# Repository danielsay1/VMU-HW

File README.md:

# Vehicle Measurement Unit - Hardware

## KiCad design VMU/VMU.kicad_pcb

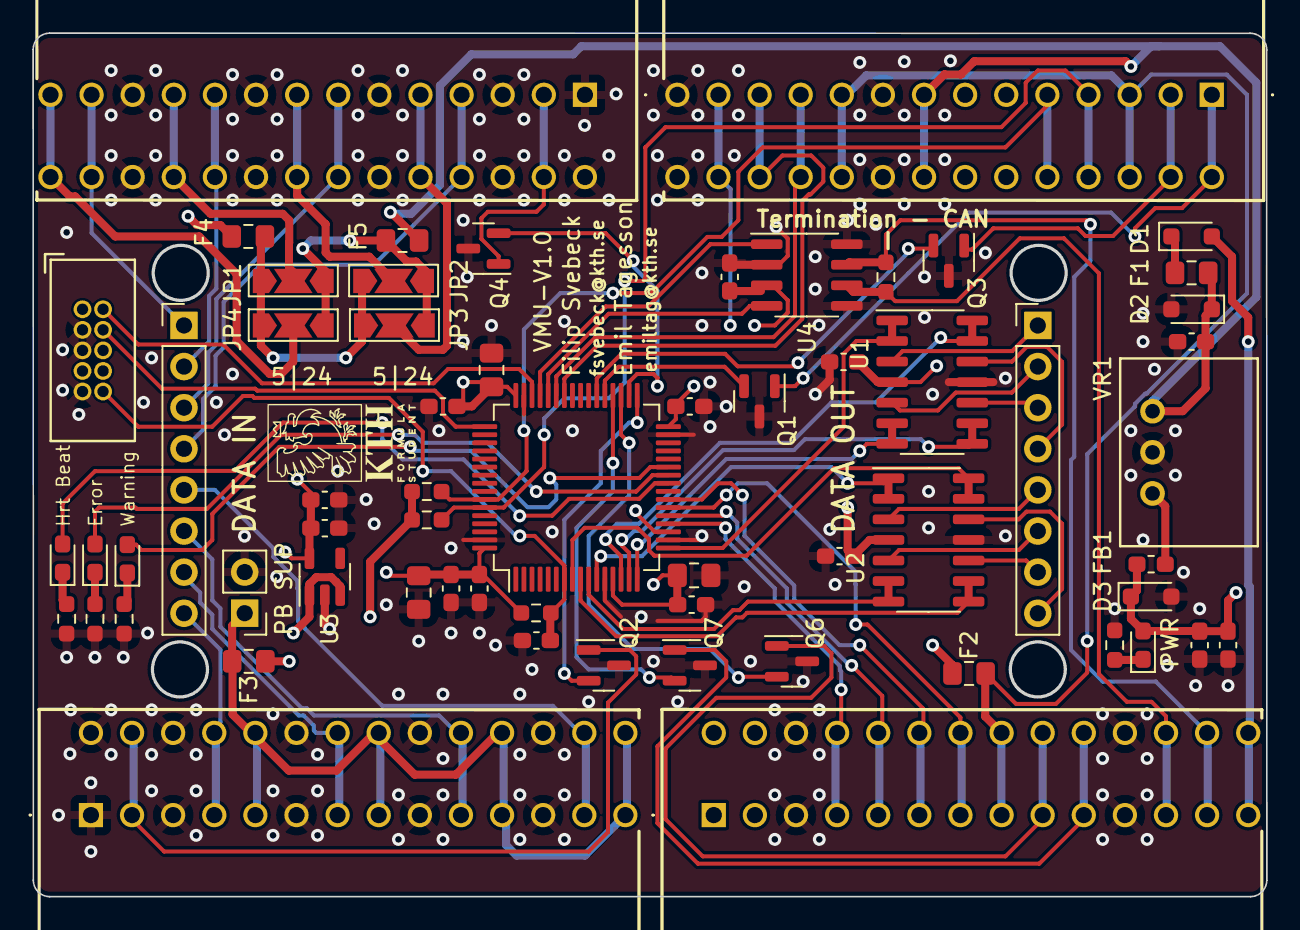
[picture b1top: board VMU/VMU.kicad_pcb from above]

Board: 4 copper layers, 76.1 x 53.2 mm, 62 parts (0 on the bottom side), 73 nets.

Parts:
C1, C2, C5, C7, C8, C9, C10, C11, C12, C13: 100n; C_0603_1608Metric_Pad1.08x0.95mm_HandSolder
C3, C4, C6: 1u; C_0603_1608Metric_Pad1.08x0.95mm_HandSolder
C14: 10n; C_0603_1608Metric_Pad1.08x0.95mm_HandSolder
C15, C16: 4.7u; C_0805_2012Metric_Pad1.18x1.45mm_HandSolder
C17: 1u; C_0805_2012Metric_Pad1.18x1.45mm_HandSolder
D1: D_Schottky; D_SOD-323_HandSoldering
D2, D3: D_TVS; D_SOD-323_HandSoldering
F1, F2, F3, F4, F5: Fuse; Fuse_0805_2012Metric_Pad1.15x1.40mm_HandSolder
FB1: FerriteBead; L_0603_1608Metric_Pad1.05x0.95mm_HandSolder
J1, J2, J6, J7: TBL009-254-14GY-2GY; TBL00925414GY2GY
J3, J4: Conn_01x08_Pin; PinHeader_1x08_P2.54mm_Vertical
J5: Conn_01x02_Pin; PinHeader_1x02_P2.54mm_Vertical
J8: ARM_JTAG_SWD_10; Atmel_ICP_connector
JP1, JP2, JP3, JP4: Jumper_3_Open; SolderJumper-3_P2.0mm_Open_TrianglePad1.0x1.5mm_NumberLabels
Q1, Q2, Q3, Q4, Q6, Q7: NMOS; SOT-23
R1: 510; R_0603_1608Metric_Pad0.98x0.95mm_HandSolder
R2: 120; R_0603_1608Metric_Pad0.98x0.95mm_HandSolder
R3: 10k; R_0603_1608Metric_Pad0.98x0.95mm_HandSolder
R4, R5, R6: 1k; R_0603_1608Metric_Pad0.98x0.95mm_HandSolder
R7, R8: 2k7; R_0603_1608Metric_Pad0.98x0.95mm_HandSolder
U1, U2: TLV9064; SOIC-14_3.9x8.7mm_P1.27mm
U3: ADP150AUJZ-3.3-R7; SOT-23-5
U4: SN65HVD233; SOIC-8_3.9x4.9mm_P1.27mm
U5: STM32F091RCTx; LQFP-64_10x10mm_P0.5mm
VR1: Wurth-FDSM
locked: BLUE; D_0603_1608Metric_Pad1.05x0.95mm_HandSolder
locked#2: YELLOW; D_0603_1608Metric_Pad1.05x0.95mm_HandSolder
locked#3, locked#4: RED; D_0603_1608Metric_Pad1.05x0.95mm_HandSolder

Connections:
+3.3V: C6.1, C7.1, C8.2, C10.1, C11.1, C12.1, C13.1, C14.1, C15.1, C16.1, C17.1, J2.25, J2.26, J8.1 (VTref), R3.1, U3.5 (VOUT), U4.3 (VCC), U5.13 (VDDA), U5.19 (VDD), U5.32 (VDD), U5.48 (VDDIO2), U5.64 (VDD)
+5V: C1.1, C2.1, C4.1, C5.1, D3.1 (A1), F2.1, F3.1, F4.1, FB1.2, J2.11, J2.12, J2.13, J2.14, J6.1, J6.2, J6.3, J6.4, R7.1, R8.1, U1.4 (V+), U2.4 (V+), U3.1 (VIN), U3.3 (EN), locked#4.2 (A)
+24V: C3.1, D2.1 (A1), F1.1, F5.1, J2.15, J2.16, VR1.1 (IN)
/ANALOG_1_SIGNAL: J1.25, J1.26, J3.1
/ANALOG_2_SIGNAL: J1.19, J1.20, J3.2
/ANALOG_3_SIGNAL: J1.13, J1.14, J3.3
/ANALOG_4_SIGNAL: J1.7, J1.8, J3.4
/ANALOG_5_SIGNAL: J3.5, J7.25, J7.26
/ANALOG_6_SIGNAL: J3.6, J7.19, J7.20
/ANALOG_7_SIGNAL: J3.7, J7.13, J7.14
/ANALOG_8_SIGNAL: J3.8, J7.7, J7.8
/CAN1_H: J6.25, J6.26, R2.1, U4.7 (CANH)
/CAN1_L: J6.23, J6.24, R2.2, U4.6 (CANL)
/DIGITAL_SUPPLY_1: F2.2, J2.5, J2.6, J2.19, J2.20, J6.15, J6.16
/GPIO_GND_1: J7.3, J7.4, Q2.1 (D)
/GPIO_GND_2: J1.3, J1.4, Q4.1 (D)
/GPIO_GND_3: J6.17, J6.18, Q6.1 (D)
/GPIO_GND_4: J6.19, J6.20, Q7.1 (D)
/GPIO_GND_5: J2.1, J2.2, Q1.1 (D)
/GPIO_GND_6: J2.3, J2.4, Q3.1 (D)
/I2C_SCL: J2.9, J2.10, R8.2, U5.58 (PB6)
/I2C_SDA: J2.7, J2.8, R7.2, U5.59 (PB7)
/MCU/ANALOG_1: U1.1, U1.2 (-), U5.17 (PA3)
/MCU/ANALOG_2: U1.6 (-), U1.7, U5.16 (PA2)
/MCU/ANALOG_3: U1.8, U1.9 (-), U5.15 (PA1)
/MCU/ANALOG_4: U1.13 (-), U1.14, U5.14 (PA0)
/MCU/ANALOG_5: U2.1, U2.2 (-), U5.11 (PC3)
/MCU/ANALOG_6: U2.6 (-), U2.7, U5.10 (PC2)
/MCU/ANALOG_7: U2.8, U2.9 (-), U5.9 (PC1)
/MCU/ANALOG_8: U2.13 (-), U2.14, U5.8 (PC0)
/MCU/CAN_RX: U4.4 (R), U5.44 (PA11)
/MCU/CAN_TX: U4.1 (D), U5.45 (PA12)
/MCU/STATUS_LED_1_LED: U5.25 (PC5), locked#2.2 (A)
/MCU/STATUS_LED_2_LED: U5.27 (PB1), locked.2 (A)
/MCU/STATUS_LED_3_LED: U5.26 (PB0), locked#3.2 (A)
/MCU/swdclk: J8.4 (SWDCLK/TCK), U5.49 (PA14)
/MCU/swdio: J8.2 (SWDIO/TMS), U5.46 (PA13)
/MCU/~reset: C9.1, J8.10 (~RESET), R3.2, U5.7 (NRST)
/PB_SUPPLY: F3.2, J5.1, J7.9, J7.10, J7.15, J7.16, J7.21, J7.22, J7.27, J7.28
/SPI_MISO: J6.13, J6.14, U5.22 (PA6)
/SPI_MOSI: J6.11, J6.12, U5.23 (PA7)
/SPI_SCLK: J6.9, J6.10, U5.21 (PA5)
/SPI_~CS: J6.7, J6.8, U5.20 (PA4)
/SUPPLY_1: J1.27, J1.28, JP4.2 (C)
/SUPPLY_2: J1.21, J1.22, JP1.2 (C)
/SUPPLY_3: J1.15, J1.16, JP2.2 (C)
/SUPPLY_4: J1.9, J1.10, JP3.2 (C)
/UART_RX: J2.21, J2.22, U5.43 (PA10)
/UART_TX: J2.23, J2.24, U5.42 (PA9)
/battery_in: D1.2 (A), J6.27, J6.28
GND: C1.2, C2.2, C3.2, C4.2, C5.2, C6.2, C7.2, C8.1, C9.2, C10.2, C11.2, C12.2, C13.2, C14.2, C15.2, C16.2, C17.2, D2.2 (A2), D3.2 (A2), J1.1, J1.2, J1.5, J1.6, J1.11, J1.12, J1.17, J1.18, J1.23, J1.24, J2.17, J2.18, J2.27, J2.28, J5.2, J6.5, J6.6, J6.21, J6.22, J7.1, J7.2, J7.5, J7.6, J7.11, J7.12, J7.17, J7.18, J7.23, J7.24, J8.3 (GND), J8.5 (GND), J8.9 (GNDDetect), Q1.3 (S), Q2.3 (S), Q3.3 (S), Q4.3 (S), Q6.3 (S), Q7.3 (S), R1.2, R4.1, R5.1, R6.1, U1.11 (V-), U2.11 (V-), U3.2 (GND), U4.2 (GND), U4.5 (LBK), U4.8 (Rs), U5.12 (VSSA), U5.18 (VSS), U5.31 (VSS), U5.47 (VSS), U5.63 (VSS), VR1.2 (GND)
unnamed: D1.1 (K), F1.2
unnamed: R1.1, locked#4.1 (K)
unnamed: R4.2, locked.1 (K)
unnamed: R5.2, locked#2.1 (K)
unnamed: R6.2, locked#3.1 (K)
unnamed: J4.1, U1.3 (+)
unnamed: J4.2, U1.5 (+)
unnamed: J4.3, U1.10 (+)
unnamed: J4.4, U1.12 (+)
unnamed: J4.5, U2.3 (+)
unnamed: J4.6, U2.5 (+)
unnamed: J4.7, U2.10 (+)
unnamed: J4.8, U2.12 (+)
unnamed: F4.2, JP1.1 (A), JP2.1 (A), JP3.1 (A), JP4.1 (A)
unnamed: F5.2, JP1.3 (B), JP2.3 (B), JP3.3 (B), JP4.3 (B)
unnamed: Q1.2 (G), U5.37 (PC6)
unnamed: Q2.2 (G), U5.33 (PB12)
unnamed: Q3.2 (G), U5.38 (PC7)
unnamed: Q4.2 (G), U5.34 (PB13)
unnamed: Q6.2 (G), U5.35 (PB14)
unnamed: Q7.2 (G), U5.36 (PB15)
unnamed: FB1.1, VR1.3 (OUT)

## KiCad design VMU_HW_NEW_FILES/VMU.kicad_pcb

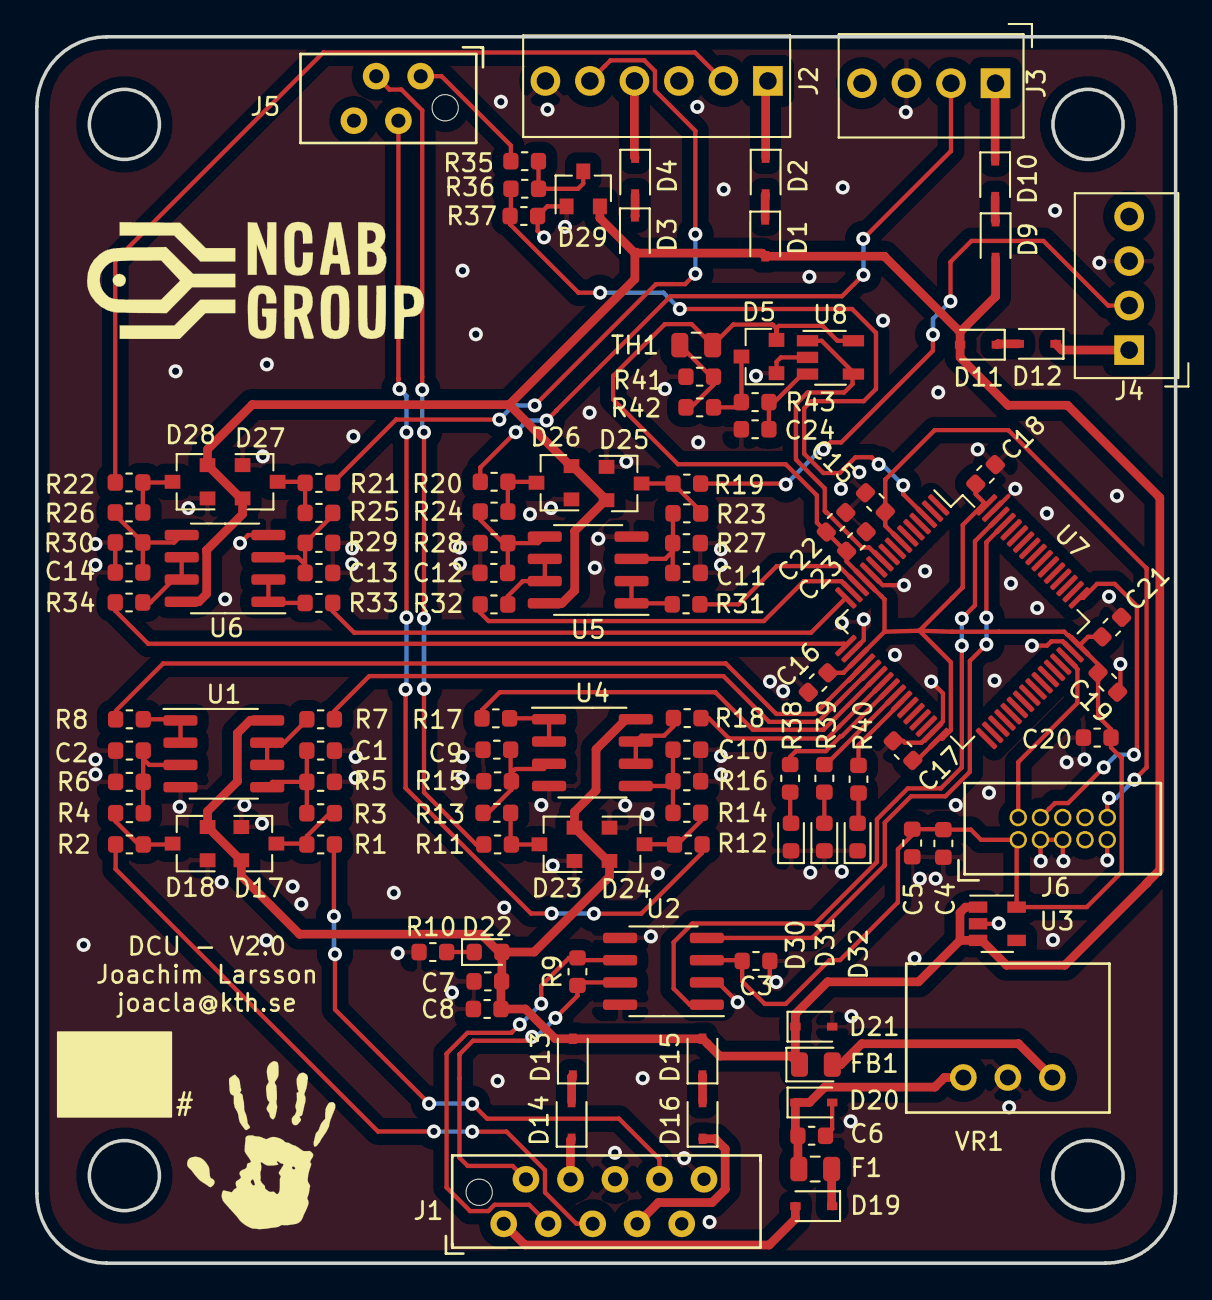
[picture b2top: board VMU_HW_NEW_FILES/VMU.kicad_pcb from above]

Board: 2 copper layers, 65.0 x 70.0 mm, 114 parts (0 on the bottom side), 80 nets.

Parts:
C1, C2, C9, C10, C11, C12, C13, C14: 22n; C_0603_1608Metric
C3, C5, C8, C15, C16, C17, C18, C19, C24: 100n; C_0603_1608Metric
C4, C6, C7, C23: 1u; C_0603_1608Metric
C20, C21: 4.7u; C_0603_1608Metric
C22: 10n; C_0603_1608Metric
D1, D2, D3, D4, D9, D10, D11, D12, D13, D14, D15, D16: D; D_SOD-323
D5, D17, D18, D23, D24, D25, D26, D27, D28, D29: D_Schottky_x2_Serial_AKC; SOT-23
D19: SCHOTTKEY; D_SOD-323
D20, D21: TVS; D_SOD-323
D22: RED; LED_0603_1608Metric
D30: GREEN; LED_0603_1608Metric
D31: YELLOW; LED_0603_1608Metric
D32: BLUE; LED_0603_1608Metric
F1: Fuse; Fuse_0805_2012Metric
FB1: Ferrite_Bead; D_0805_2012Metric
J1: Conn_01x10_Female; Wurth-MM_female_10
J2: Conn_01x06_Female; Wurth-WTB_2.54_male_vert_6
J3: Conn_01x04_Male; Wurth-WTB_2.54_male_vert_4
J4: Conn_01x04_Female; Wurth-WTB_2.54_male_vert_4
J5: Conn_01x04_Female; Wurth-MM_female_4
J6: ARM_JTAG_SWD_10; Atmel_ICP_connector
R1, R2, R3, R4, R11, R12, R13, R14, R19, R20, R21, R22, R23, R24, R25, R26, R35: 200; R_0603_1608Metric
R5, R6, R10, R15, R16, R27, R28, R29, R30, R37: 510; R_0603_1608Metric
R7, R8, R17, R18, R31, R32, R33, R34, R42: 100; R_0603_1608Metric
R9: 120; R_0603_1608Metric
R36: 51; R_0603_1608Metric
R38, R39, R40, R43: 1k; R_0603_1608Metric
R41: 10k; R_0603_1608Metric
TH1: 10k; R_0805_2012Metric
U1, U4, U5, U6: LM358; SOIC-8_3.9x4.9mm_P1.27mm
U2: SN65HVD233; SOIC-8_3.9x4.9mm_P1.27mm
U3: ADP150AUJZ-3.3-R7; SOT-23-5
U7: STM32F091RCTx; LQFP-64_10x10mm_P0.5mm
U8: TLV9061; TSOT-23-5
VR1: Wurth-FDSM

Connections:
+3V3: C3.2, C4.1, C5.1, C16.1, C17.1, C18.1, C19.1, C20.1, C21.1, C22.1, C23.1, D5.2, J6.1, TH1.1, U2.3, U3.5, U7.13, U7.19, U7.32, U7.48, U7.64, U8.5
+5V: C7.1, C8.1, D1.2, D3.2, D9.2, D11.2, D13.2, D15.2, D17.2, D18.2, D21.1, D22.2, D23.2, D24.2, D25.2, D26.2, D27.2, D28.2, D29.2, FB1.1, U1.8, U3.1, U3.3, U4.8, U5.8, U6.8
+24V: C6.1, D20.1, F1.1, VR1.1
/APPS1_SIGNAL: J3.2, R20.2
/APPS1_SUPPLY: D10.1, J3.1
/APPS2_SIGNAL: J4.2, R19.2
/APPS2_SUPPLY: D12.1, J4.1
/BPPS1_SIGNAL: J2.2, R22.2
/BPPS1_SUPPLY: D2.1, J2.1
/BPPS2_SIGNAL: J2.5, R21.2
/BPPS2_SUPPLY: D4.1, J2.4
/BRAKE_PRESSURE_1_SIGNAL: J5.2, R12.2
/BRAKE_PRESSURE_2_SIGNAL: J5.3, R11.2
/BSPD_TRIGGERED_SIGNAL: J5.1, R35.2
/CAN1_H: J1.2, R9.1, U2.7
/CAN1_L: J1.3, R9.2, U2.6
/CONTROL_SYSTEMS_SUPPLY: D19.2, J1.1
/MCU/APPS1: R32.1, U7.15
/MCU/APPS2: R31.1, U7.14
/MCU/BPPS1: R34.1, U7.17
/MCU/BPPS2: R33.1, U7.16
/MCU/BRAKE_PRESSURE_1: R18.1, U7.23
/MCU/BRAKE_PRESSURE_2: R17.1, U7.22
/MCU/BSPD_TRIGGERED: R36.1, R37.2, U7.3
/MCU/CAN1_RX: U2.4, U7.61
/MCU/CAN1_TX: U2.1, U7.62
/MCU/JTAG_RESET_N: C15.1, J6.10, U7.7
/MCU/JTAG_SWDCLK: J6.4, U7.49
/MCU/JTAG_SWDIO: J6.2, U7.46
/MCU/MCU_STATUS_LED_1: R38.2, U7.24
/MCU/MCU_STATUS_LED_2: R39.2, U7.25
/MCU/MCU_STATUS_LED_3: R40.2, U7.26
/MCU/PCB_TEMPERATURE: U7.10, U8.1, U8.4
/MCU/STEERING_ANGLE_1: R8.1, U7.20
/MCU/STEERING_ANGLE_2: R7.1, U7.21
/STEERING_ANGLE_1_SIGNAL: J1.5, R2.2
/STEERING_ANGLE_1_SUPPLY: D14.1, J1.4
/STEERING_ANGLE_2_SIGNAL: J1.8, R1.2
/STEERING_ANGLE_2_SUPPLY: D16.1, J1.7
GND: C1.2, C2.2, C3.1, C4.2, C5.2, C6.2, C7.2, C8.2, C9.2, C10.2, C11.2, C12.2, C13.2, C14.2, C15.2, C16.2, C17.2, C18.2, C19.2, C20.2, C21.2, C22.2, C23.2, C24.2, D5.1, D17.1, D18.1, D20.2, D21.2, D23.1, D24.1, D25.1, D26.1, D27.1, D28.1, D29.1, D30.1, D31.1, D32.1, J1.6, J1.9, J1.10, J2.3, J2.6, J3.3, J4.3, J6.3, J6.5, J6.9, R5.2, R6.2, R10.2, R15.2, R16.2, R27.2, R28.2, R29.2, R30.2, R37.1, R41.1, U1.4, U2.2, U2.5, U2.8, U3.2, U4.4, U5.4, U6.4, U7.12, U7.18, U7.31, U7.47, U7.63, U8.2, VR1.2
unnamed: C1.1, R3.1, R5.1, U1.5
unnamed: C2.1, R4.1, R6.1, U1.3
unnamed: C9.1, R13.1, R15.1, U4.3
unnamed: C10.1, R14.1, R16.1, U4.5
unnamed: C11.1, R23.1, R27.1, U5.3
unnamed: C12.1, R24.1, R28.1, U5.5
unnamed: C13.1, R25.1, R29.1, U6.3
unnamed: C14.1, R26.1, R30.1, U6.5
unnamed: C24.1, R43.1, U8.3
unnamed: D1.1, D2.2
unnamed: D3.1, D4.2
unnamed: D5.3, R42.1, R43.2
unnamed: D9.1, D10.2
unnamed: D11.1, D12.2
unnamed: D13.1, D14.2
unnamed: D15.1, D16.2
unnamed: D17.3, R1.1, R3.2
unnamed: D18.3, R2.1, R4.2
unnamed: D19.1, F1.2
unnamed: D22.1, R10.1
unnamed: D23.3, R11.1, R13.2
unnamed: D24.3, R12.1, R14.2
unnamed: D25.3, R19.1, R23.2
unnamed: D26.3, R20.1, R24.2
unnamed: D27.3, R21.1, R25.2
unnamed: D28.3, R22.1, R26.2
unnamed: D29.3, R35.1, R36.2
unnamed: D30.2, R38.1
unnamed: D31.2, R39.1
unnamed: D32.2, R40.1
unnamed: FB1.2, VR1.3
unnamed: R7.2, U1.6, U1.7
unnamed: R8.2, U1.1, U1.2
unnamed: R17.2, U4.1, U4.2
unnamed: R18.2, U4.6, U4.7
unnamed: R31.2, U5.1, U5.2
unnamed: R32.2, U5.6, U5.7
unnamed: R33.2, U6.1, U6.2
unnamed: R34.2, U6.6, U6.7
unnamed: R41.2, R42.2, TH1.2

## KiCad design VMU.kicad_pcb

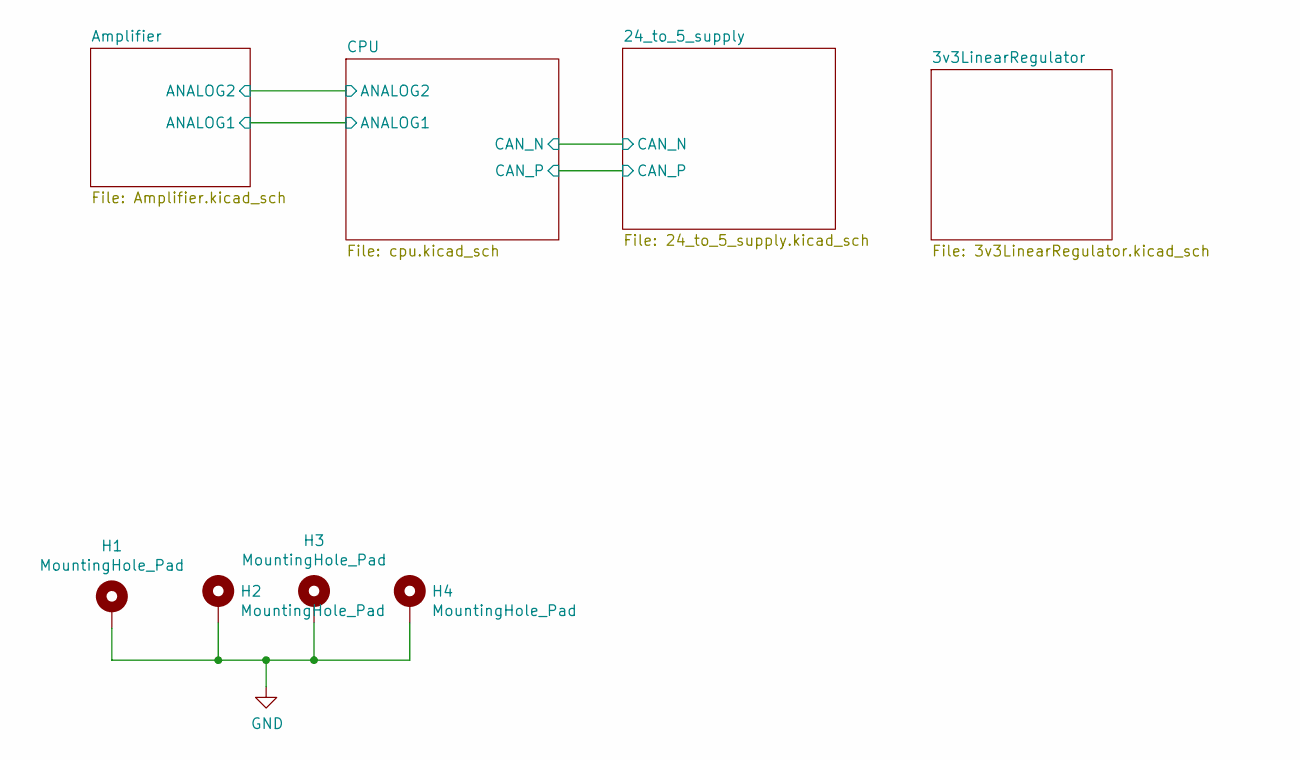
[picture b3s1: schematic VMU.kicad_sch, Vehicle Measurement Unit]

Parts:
H1, H2, H3, H4: MountingHole_Pad; MountingHole_3.2mm_M3_ISO7380_Pad

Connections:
GND: H1.1, H2.1, H3.1, H4.1; also elsewhere on the board

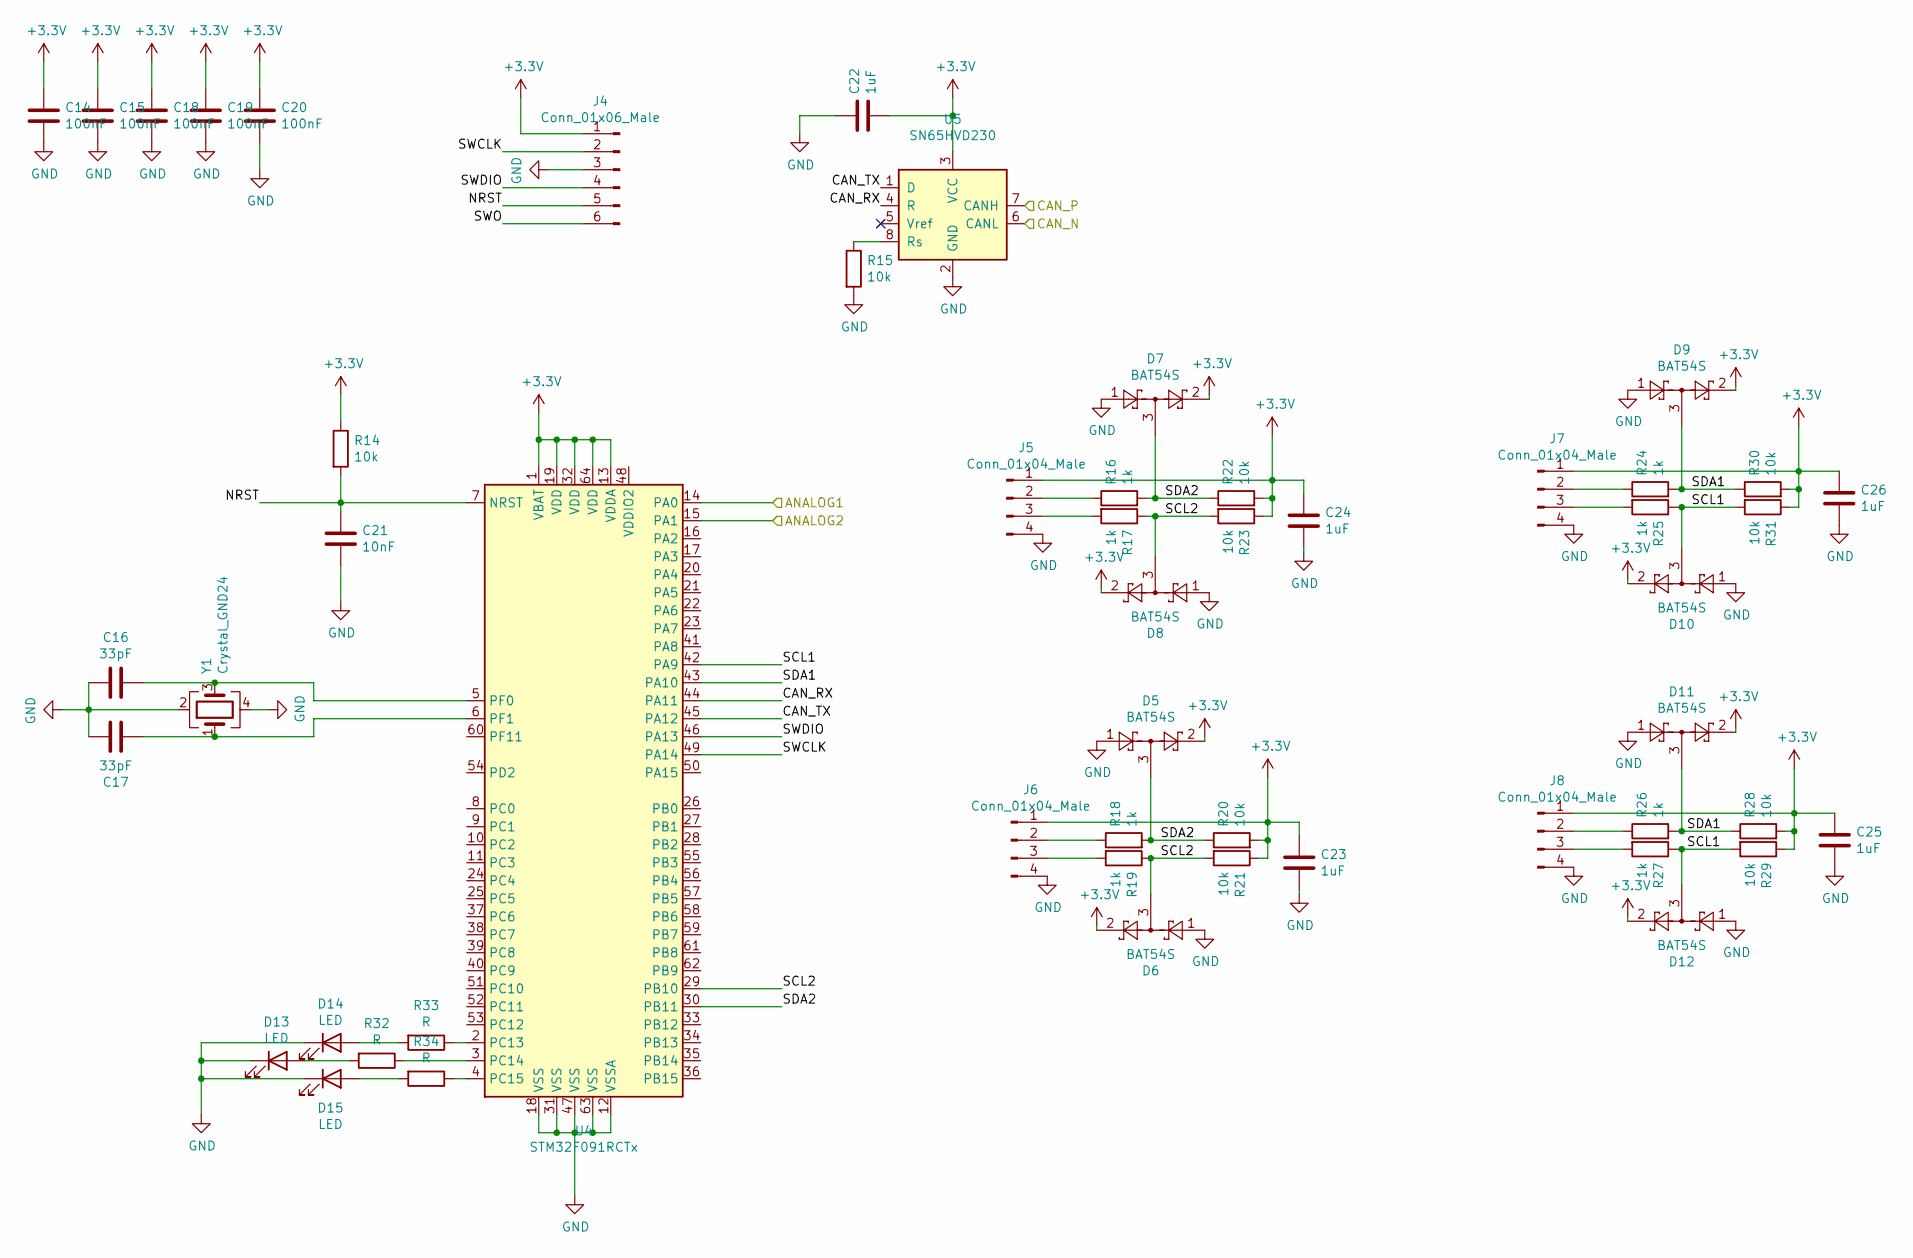
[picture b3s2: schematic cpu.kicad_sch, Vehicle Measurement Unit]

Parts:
C14, C15, C18, C19, C20: 100nF; C_0603_1608Metric
C16, C17: 33pF; C_0603_1608Metric
C21: 10nF; C_0603_1608Metric
C22, C23, C24, C25, C26: 1uF; C_0603_1608Metric
D5, D6, D7, D8, D9, D10, D11, D12: BAT54S; SOT-23
D13, D14, D15: LED; LED_0603_1608Metric
J4: Conn_01x06_Male; PinHeader_1x06_P2.54mm_Vertical
J5, J6, J7, J8: Conn_01x04_Male; Wurth-MM_female_4
R14, R15, R20, R21, R22, R23, R28, R29, R30, R31: 10k; R_0603_1608Metric
R16, R17, R18, R19, R24, R25, R26, R27: 1k; R_0603_1608Metric
R32, R33, R34: R; R_0603_1608Metric
U4: STM32F091RCTx; LQFP-64_10x10mm_P0.5mm
U5: SN65HVD230; SOIC-8_3.9x4.9mm_P1.27mm
Y1: Crystal_GND24; Crystal_SMD_3225-4Pin_3.2x2.5mm_HandSoldering

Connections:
+3V3: C14.1, C15.1, C18.1, C19.1, C20.1, C22.2, C23.1, C24.1, C25.1, C26.1, D5.2, D6.2, D7.2, D8.2, D9.2, D10.2, D11.2, D12.2, J4.1, J5.1, J6.1, J7.1, J8.1, R14.1, R20.2, R21.1, R22.2, R23.1, R28.2, R29.1, R30.2, R31.1, U4.1 (VBAT), U4.13 (VDDA), U4.19 (VDD), U4.32 (VDD), U4.64 (VDD), U5.3 (VCC); also elsewhere on the board
/24_to_5_supply/CAN_N: U5.6 (CANL); also elsewhere on the board
/24_to_5_supply/CAN_P: U5.7 (CANH); also elsewhere on the board
/Amplifier/ANALOG1: U4.14 (PA0); also elsewhere on the board
/Amplifier/ANALOG2: U4.15 (PA1); also elsewhere on the board
/CPU/CAN_RX: U4.44 (PA11), U5.4 (R)
/CPU/CAN_TX: U4.45 (PA12), U5.1 (D)
/CPU/NRST: C21.1, J4.5, R14.2, U4.7 (NRST)
/CPU/SCL1: D10.3, D12.3, R25.1, R27.1, R29.2, R31.2, U4.42 (PA9)
/CPU/SCL2: D6.3, D8.3, R17.1, R19.1, R21.2, R23.2, U4.29 (PB10)
/CPU/SDA1: D9.3, D11.3, R24.2, R26.2, R28.1, R30.1, U4.43 (PA10)
/CPU/SDA2: D5.3, D7.3, R16.2, R18.2, R20.1, R22.1, U4.30 (PB11)
/CPU/SWCLK: J4.2, U4.49 (PA14)
/CPU/SWDIO: J4.4, U4.46 (PA13)
/CPU/SWO: J4.6
GND: C14.2, C15.2, C16.2, C17.1, C18.2, C19.2, C20.2, C21.2, C22.1, C23.2, C24.2, C25.2, C26.2, D5.1, D6.1, D7.1, D8.1, D9.1, D10.1, D11.1, D12.1, D13.1 (K), D14.1 (K), D15.1 (K), J4.3, J5.4, J6.4, J7.4, J8.4, R15.2, U4.12 (VSSA), U4.18 (VSS), U4.31 (VSS), U4.47 (VSS), U4.63 (VSS), U5.2 (GND), Y1.2, Y1.4; also elsewhere on the board
unnamed: C16.1, U4.5 (PF0), Y1.3
unnamed: C17.2, U4.6 (PF1), Y1.1
unnamed: D13.2 (A), R32.2
unnamed: D14.2 (A), R33.2
unnamed: D15.2 (A), R34.2
unnamed: J5.2, R16.1
unnamed: J5.3, R17.2
unnamed: J6.2, R18.1
unnamed: J6.3, R19.2
unnamed: J7.2, R24.1
unnamed: J7.3, R25.2
unnamed: J8.2, R26.1
unnamed: J8.3, R27.2
unnamed: R15.1, U5.8 (Rs)
unnamed: R32.1, U4.3 (PC14)
unnamed: R33.1, U4.2 (PC13)
unnamed: R34.1, U4.4 (PC15)

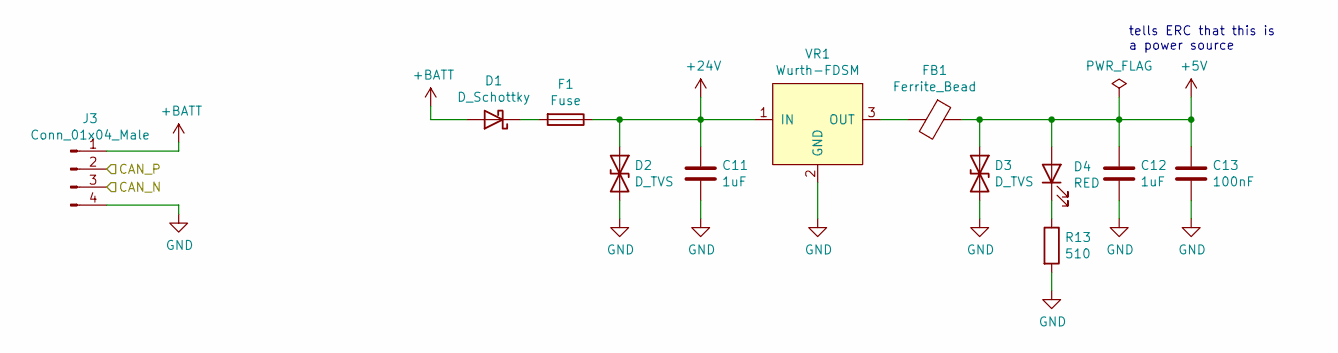
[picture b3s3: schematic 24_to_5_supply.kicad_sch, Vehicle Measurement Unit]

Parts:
C11, C12: 1uF; C_0805_2012Metric
C13: 100nF; C_0603_1608Metric
D1: D_Schottky; D_SOD-323
D2, D3: D_TVS; D_SOD-323
D4: RED; LED_0603_1608Metric
F1: Fuse; Fuse_1210_3225Metric
FB1: Ferrite_Bead; L_0805_2012Metric
J3: Conn_01x04_Male; Wurth-MM_female_4
R13: 510; R_0603_1608Metric
VR1: Wurth-FDSM

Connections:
+5V: C12.1, C13.1, D3.1 (A1), D4.2 (A), FB1.1; also elsewhere on the board
+24V: C11.1, D2.1 (A1), F1.1, VR1.1 (IN)
+BATT: D1.2 (A), J3.1
/24_to_5_supply/CAN_N: J3.3; also elsewhere on the board
/24_to_5_supply/CAN_P: J3.2; also elsewhere on the board
GND: C11.2, C12.2, C13.2, D2.2 (A2), D3.2 (A2), J3.4, R13.2, VR1.2 (GND); also elsewhere on the board
unnamed: D1.1 (K), F1.2
unnamed: D4.1 (K), R13.1
unnamed: FB1.2, VR1.3 (OUT)

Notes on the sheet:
tells ERC that this is a power source

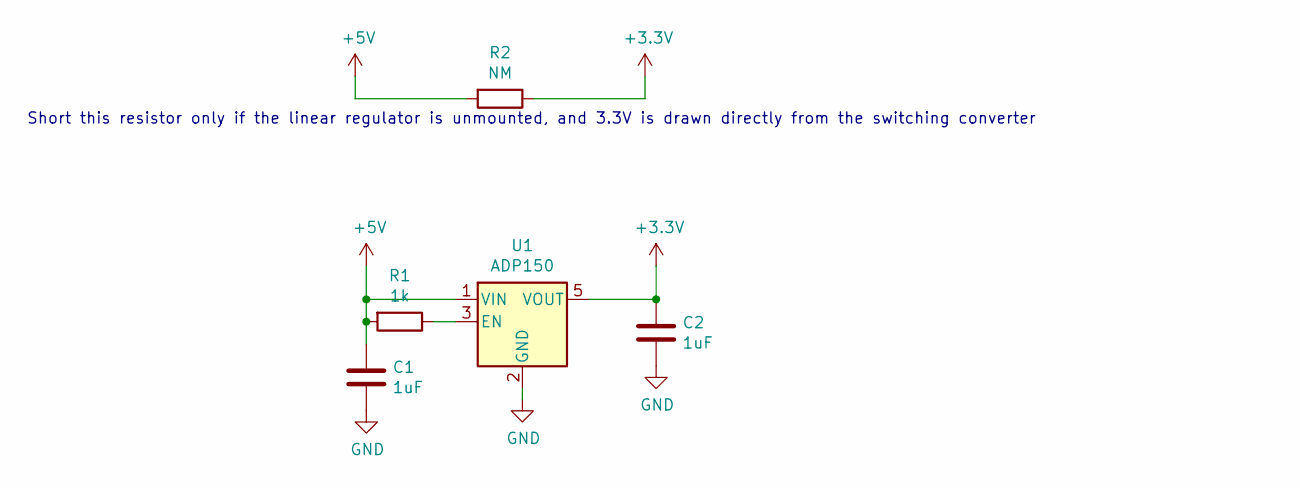
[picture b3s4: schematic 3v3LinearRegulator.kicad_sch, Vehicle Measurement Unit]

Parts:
C1, C2: 1uF; C_0603_1608Metric
R1: 1k; R_0603_1608Metric
R2: NM; R_0603_1608Metric
U1: ADP150; SOT-23-5

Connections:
+3V3: C2.1, R2.1, U1.5 (VOUT); also elsewhere on the board
+5V: C1.1, R1.2, R2.2, U1.1 (VIN); also elsewhere on the board
GND: C1.2, C2.2, U1.2 (GND); also elsewhere on the board
unnamed: R1.1, U1.3 (EN)

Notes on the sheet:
Short this resistor only if the linear regulator is unmounted, and 3.3V is drawn directly from the switching converter

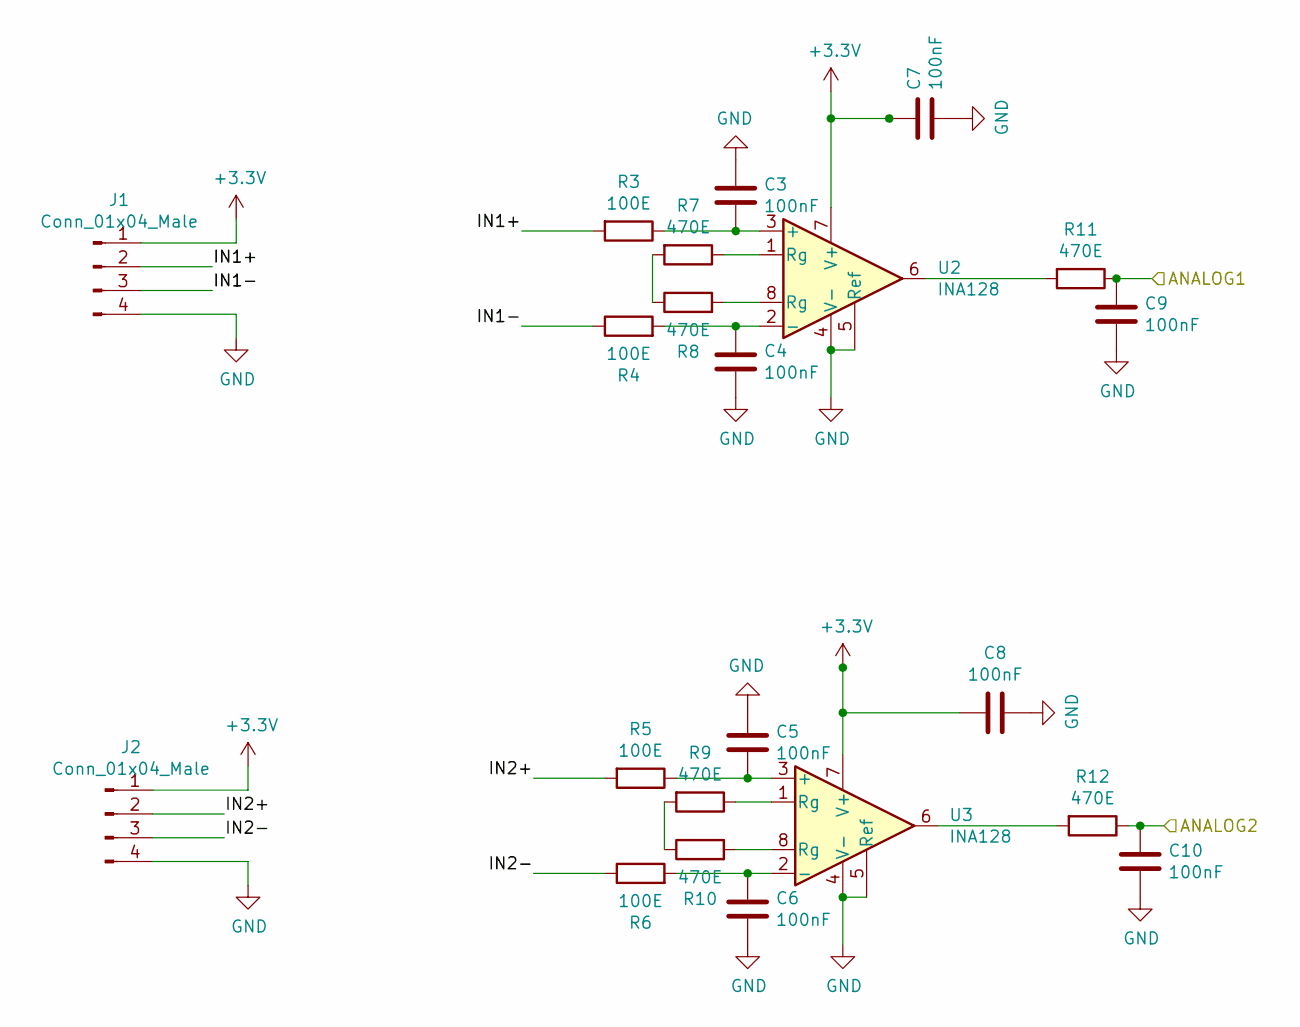
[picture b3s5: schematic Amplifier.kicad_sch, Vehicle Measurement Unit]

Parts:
C3, C4, C5, C6, C7, C8, C9, C10: 100nF; C_0603_1608Metric
J1, J2: Conn_01x04_Male; Wurth-MM_female_4
R3, R4, R5, R6: 100E; R_0603_1608Metric
R7, R8, R9, R10, R11, R12: 470E; R_0603_1608Metric
U2, U3: INA128; SOIC-8_3.9x4.9mm_P1.27mm

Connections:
+3V3: C7.1, C8.2, J1.1, J2.1, U2.7 (V+), U3.7 (V+); also elsewhere on the board
/Amplifier/ANALOG1: C9.1, R11.1; also elsewhere on the board
/Amplifier/ANALOG2: C10.1, R12.1; also elsewhere on the board
/Amplifier/IN1+: J1.2, R3.2
/Amplifier/IN1-: J1.3, R4.1
/Amplifier/IN2+: J2.2, R5.2
/Amplifier/IN2-: J2.3, R6.1
GND: C3.1, C4.2, C5.1, C6.2, C7.2, C8.1, C9.2, C10.2, J1.4, J2.4, U2.4 (V-), U2.5 (Ref), U3.4 (V-), U3.5 (Ref); also elsewhere on the board
unnamed: C3.2, R3.1, U2.3 (+)
unnamed: C4.1, R4.2, U2.2 (-)
unnamed: C5.2, R5.1, U3.3 (+)
unnamed: C6.1, R6.2, U3.2 (-)
unnamed: R7.1, U2.1 (Rg)
unnamed: R7.2, R8.1
unnamed: R8.2, U2.8 (Rg)
unnamed: R9.1, U3.1 (Rg)
unnamed: R9.2, R10.1
unnamed: R10.2, U3.8 (Rg)
unnamed: R11.2, U2.6
unnamed: R12.2, U3.6

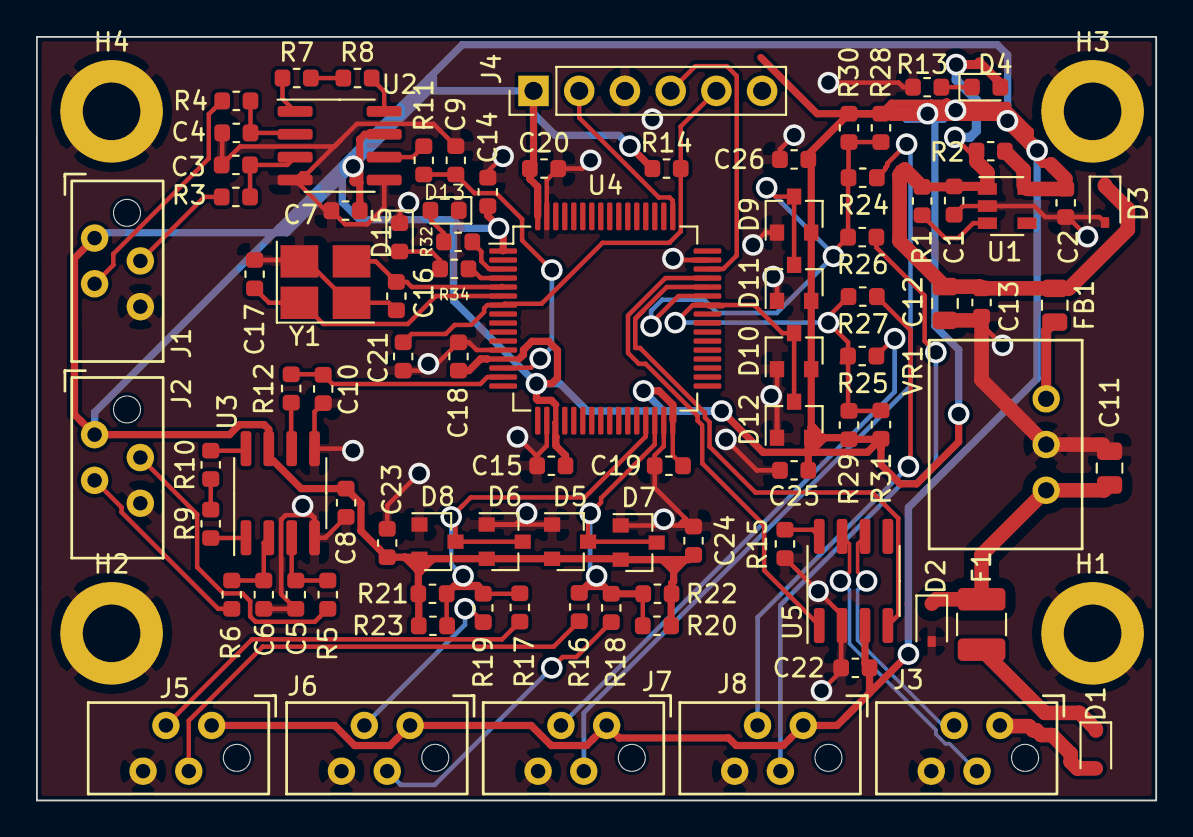
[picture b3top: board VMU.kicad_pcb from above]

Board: 2 copper layers, 62.2 x 42.4 mm, 94 parts (0 on the bottom side), 53 nets.

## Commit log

2019-11-23 Added VMU-HW.drawio
2019-12-07 Testing commit
2020-12-29 vishnu files
2023-10-19 MCU File
    Adding MCU file with changes
2023-10-19 Added new VMU and POWER file
2023-10-24 Create SIGNAL_CONDITIONING_VMU.kicad_sch
    Ny mapp:
    Skapade en ny mapp som heter VMU_HW_NEW_FILES där vi kan lägga alla nya filer till vidare och det blir då lättare för Emil att kolla på vad vi gjort. Jag vet inte vilka av de andra filerna som kan va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
    SIGNAL_CONDITIONING:
    Lagt till två power block och döpt om OP amparna.
2023-10-24 Flytta MCU till ny folder
    Flytta MCU till ny folder
2023-11-01 MCU
    New MCU
2023-11-01 MCU
    Snygga till MCU
2023-11-01 Första utkast av VMU och Power
2023-11-01 MCU agian
2023-11-02 Hjälp av Tore
2023-11-02 tog bort fel signal fil
2023-11-02 MCU FIX TORE
2023-11-02 VMU small update
2023-11-11 clean up
2023-11-11 Nytt namn SIGNAL COND
2024-02-10 VMU2024
2024-02-10 sdfsd
2024-02-11 bb
    h
2024-02-19 Adad
    a
2024-02-19 sadsadsa
2024-02-22 RotingV1
2024-02-28 RoutingV2
2024-04-11 fiixes
2024-04-16 Labels
2024-04-18 Update
    + GND vias
    less silk screen
2024-04-23 Footprint changes
    annular holewidth
2024-09-20 cleanup
2025-10-07 test pull request
2025-10-07 banana
